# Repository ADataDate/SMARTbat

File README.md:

Meet Austin: the SMARTbat

Shoulder Mounted Anxiety Relieving Therapy Bat
==================================================================

Austin, the SMARTBat, is a shoulder mounted robot that monitors the wearer's **heart rate**, **oxygen saturation**, **respiration**, and **GSR** to build a live approximate model of the level of stress experienced by the wearer and autonomoulsy administers deep touch pressure therapy through a pnuematic vest when stress levels are out of normal range. Austin also monitors the social environment with verbal feedback on the "emotion" of the room using computer vision and tone analysis and names the faces it recognizes when queried. Communicating with Austin is possible thanks to the following Google Cloud services:

- [Speech-to-Text](https://cloud.google.com/speech-to-text)
- [Text-to-Speech](https://cloud.google.com/text-to-speech)

Austin is wrapped up in an adorably-cuddleable brown bat plushie that magnetically attaches to the wearer's shoulder and is programmed with physical(gestures) and emotional(RGB LED eyes) responses.

Repository Contents
-------------------

* **/Documents** - Images, reports, presentations, papers, etc
* **/Software** - Arduino sketches, Python scripts, and Log files
* **/Hardware** - Eagle files
* **/sensors_test** - UART Communication tests between devices

Documentation
-------------
To publish and subscribe to messages via MQTT, make sure you have an environment variable **CLOUDMQTT_URL:**
```bash
export CLOUDMQTT_URL=<url of your mqtt broker>
```
Python scripts also require the Eclipse Paho MQTT Python client library to be installed:
```bash
pip install --upgrade paho-mqtt
```

### Integration (+Austin)
First plug `Arduino` to your computer or raspberry pi on which you are going to run this python script.
Upload a sketch called `Software/stress_sensors_and_austin_emotes_ctrl/AustinOutput/AustinOutput.ino` to the `Arduino`.

To receive commands from MQTT and to forward the commands to Austin, just run

```
python Software/integration/subscriber.py --serial_port=<serial port of your arduino>
```

### Belt (Currently this is still under development due to hardware issue)
The belt has a separate sketch from that of Austin's.
Please upload a sketch called `Software/motion_control/motion_control.ino` to the other Arduino on the belt.

### Facial and Emotion Recognition
See [Facial and Emotion Recognition Documentation](https://github.com/Sayter99/face_recognition_ultra_light/blob/master/README.md).

### Voice User Interface (VUI)

The VUI requires a Google Cloud service account with access to the Cloud Speech-to-Text API and Cloud Text-to-Speech API. The location of the key file for the service account should be specified with the `GOOGLE_APPLICATION_CREDENTIALS` environment variable.

The VUI works with Python 3.7.1, and the required packages specific to the VUI can be installed as follows:
```bash
pip install --upgrade google-cloud-texttospeech
pip install --upgrade google-cloud-speech
pip install --upgrade pyaudio
pip install --upgrade pygame
```

To start the VUI, run the following:
```bash
cd ./Software/voice_user_interface
python main.py
```

### Stress Classifier

The stress classifier works with Python 3.7.1, and has no additional dependencies.

To start the stress classifier, run the following:
```bash
cd ./Software/stress_classifier
python stress_classifier.py
```

### Wearable Sensors

The arduino sketch **_Sensors_** serially outputs the heart rate, blood oxygen saturation, respiration and GSR data values which is read the script **_mqtt_on_body_sensors_pub_emotions_sub_**. This script then publishes the sensor data to a broker via MQTT.

Demonstration
-------------
* **Video to come**

License Information
-------------------

This product is _**open source**_!

Distributed as-is; no warranty is given. This is not a medical device and should not be used for the detection or prevention of disease, illness or otherwise.

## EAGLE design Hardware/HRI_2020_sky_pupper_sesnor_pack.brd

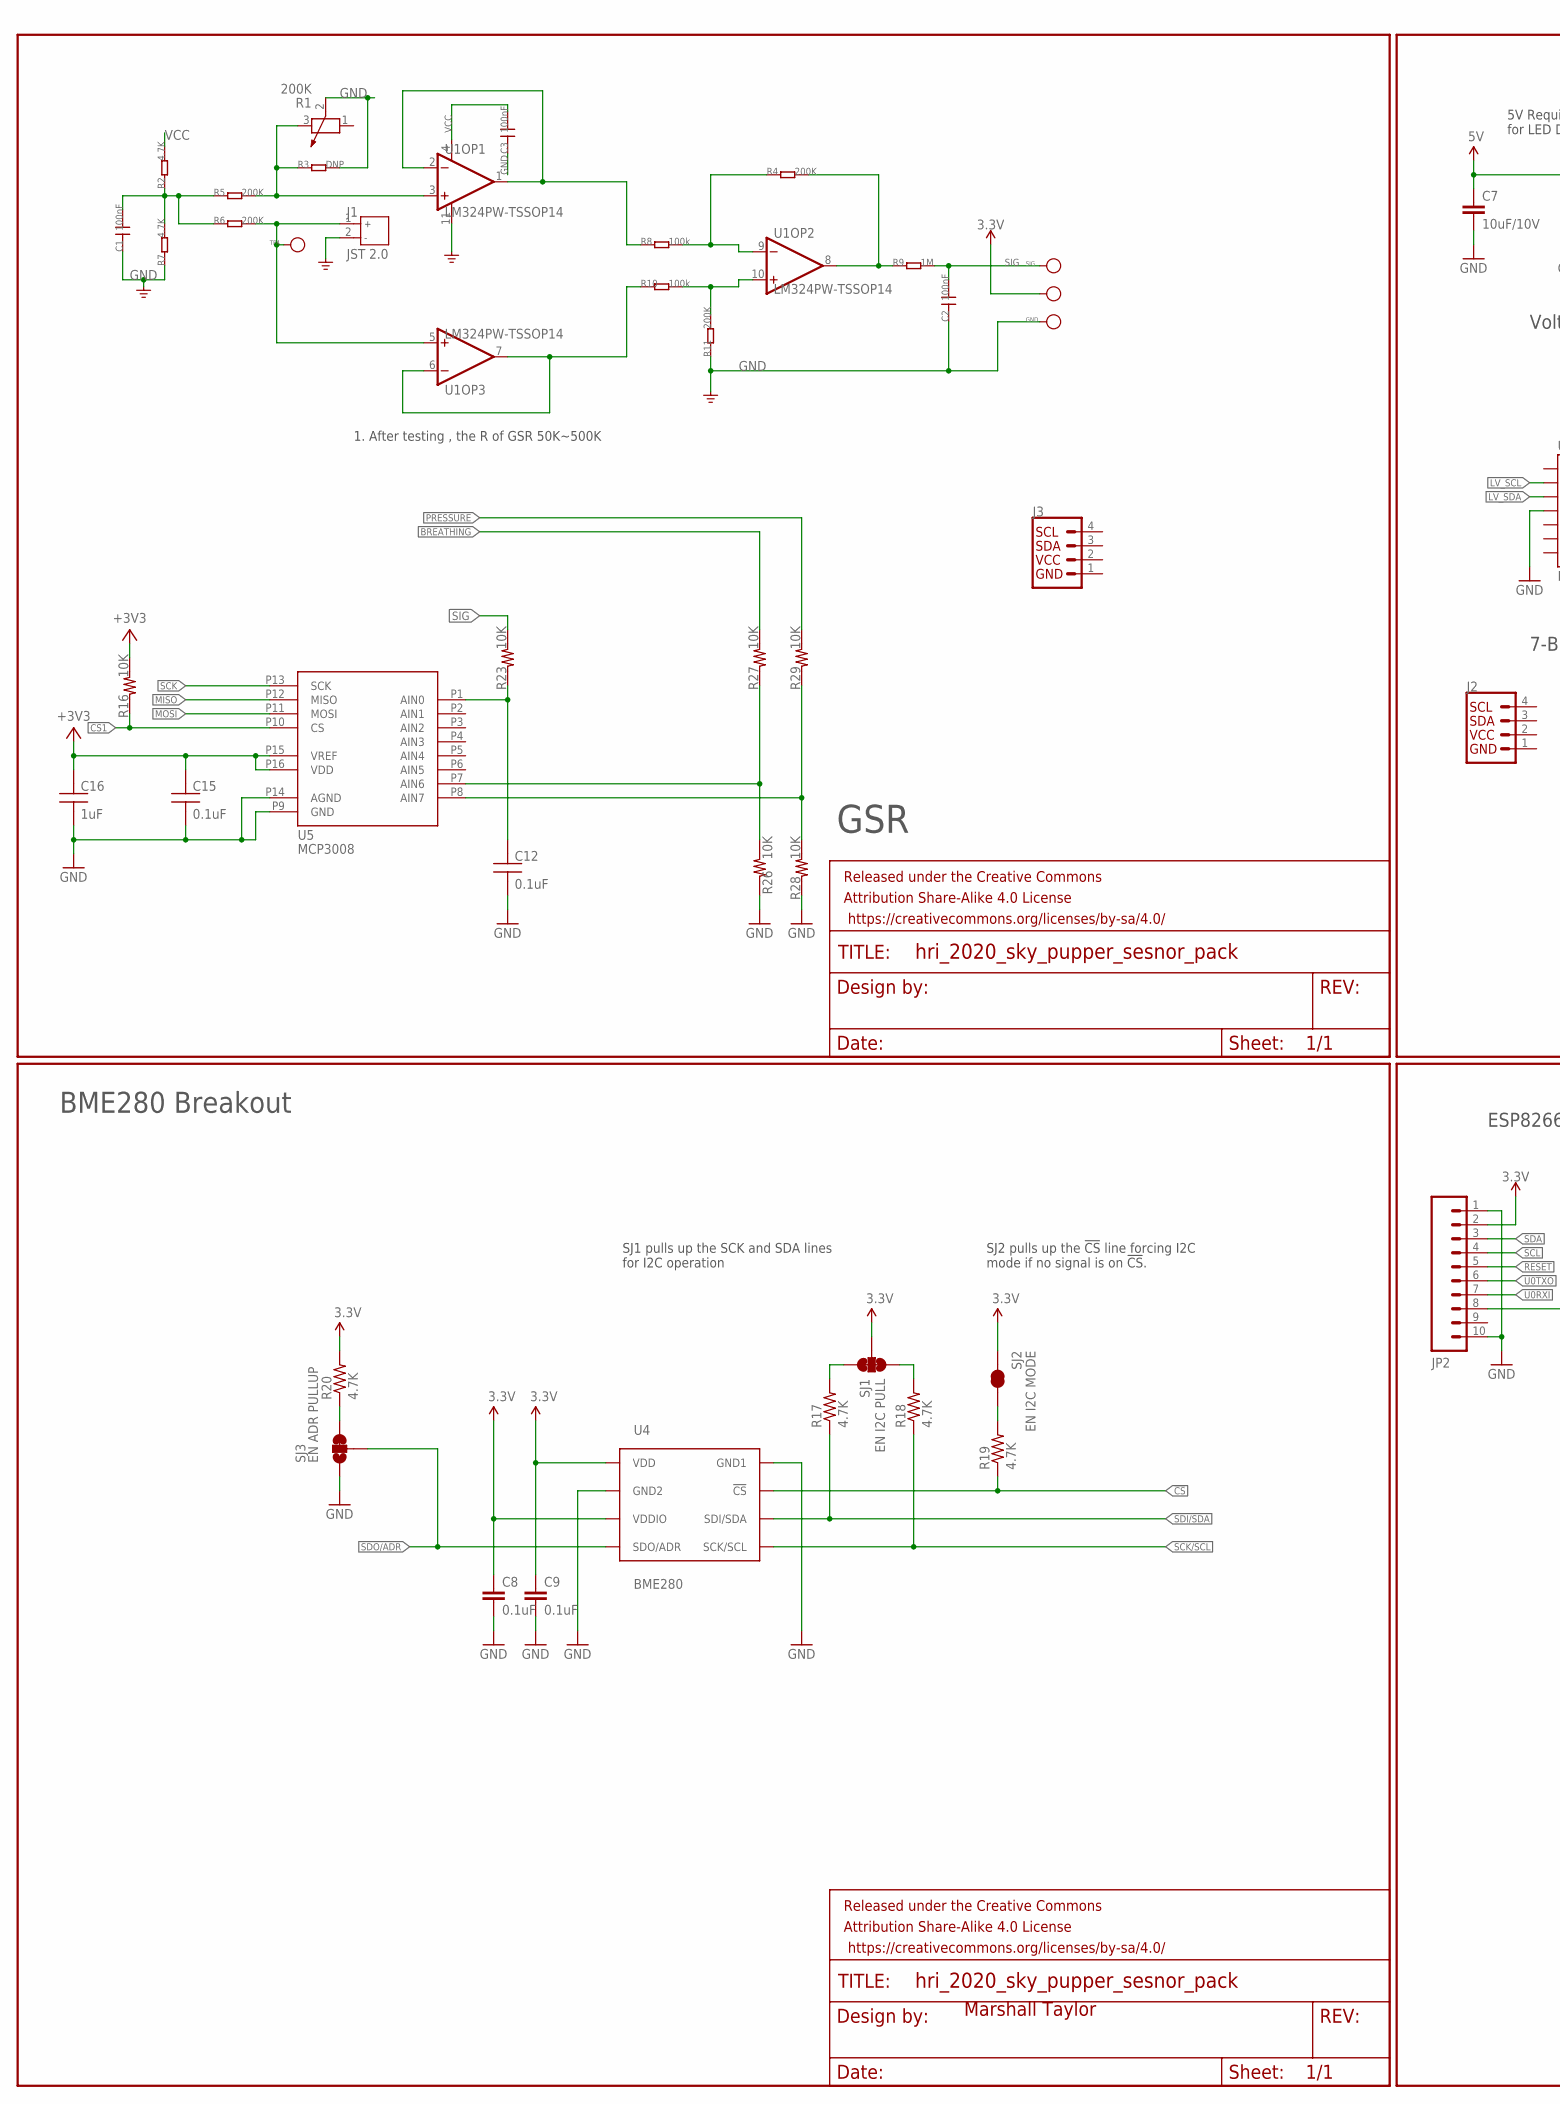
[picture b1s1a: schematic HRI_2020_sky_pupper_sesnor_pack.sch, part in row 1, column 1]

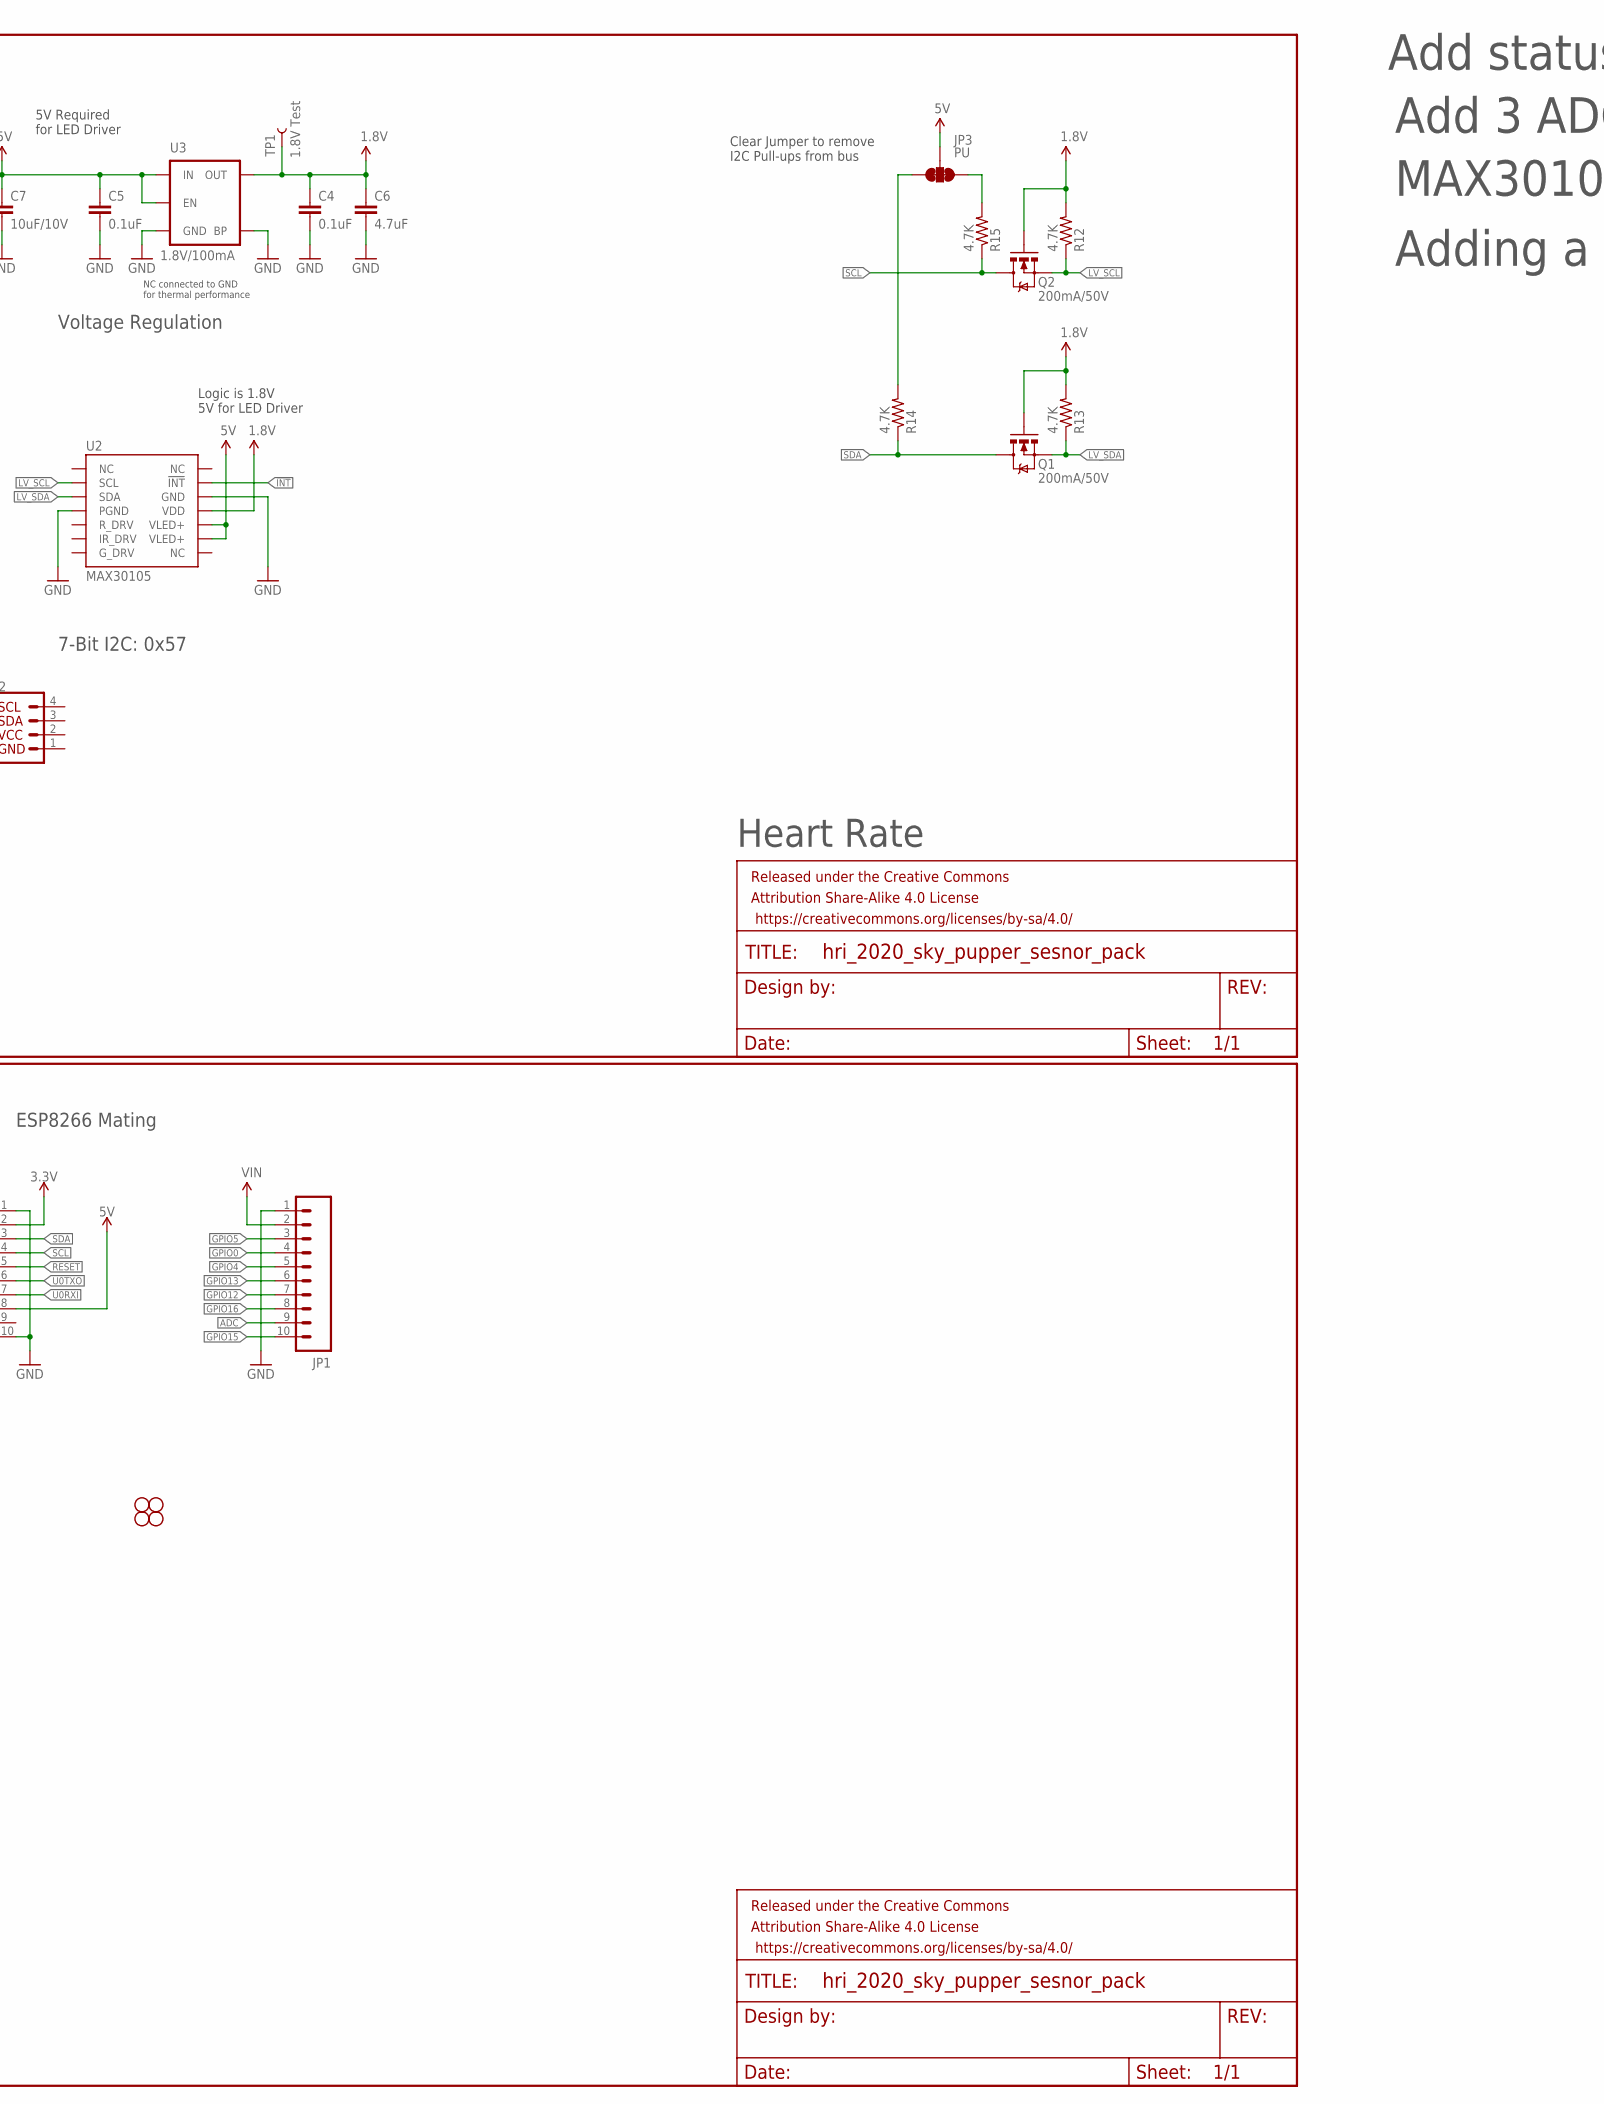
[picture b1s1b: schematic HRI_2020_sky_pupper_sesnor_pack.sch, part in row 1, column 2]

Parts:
C1, C2, C3: 100nF; 0603
C4, C5: 0.1uF; 0603-CAP@1
C6: 4.7uF; 0603-CAP@1
C7: 10uF/10V; 0805-CAP
C8, C9: 0.1uF; 0603-CAP
C12, C15: 0.1uF; 0603_SILK; PARTNO GRM188R70J104KA01D
C16: 1uF; 0603_SILK; PARTNO GRM188R70J104KA01D
FRAME1, FRAME2, FRAME3, FRAME4: FRAME-LETTERNO_PACKAGE; DUMMY
GND: PAD-TEST-POINT'4545'; TP_4545
J1: JST 2.0; JST-2.0
J2, J3: QWIIC_CONNECTORJS-1MM; 1X04_1MM_RA
JP1, JP2: M10NO_SILK_PTH_FEMALE; 1X10_NO_SILK
JP3: PU; PAD-JUMPER-3-3OF3_NC_BY_TRACE_YES_SILK_FULL_BOX
Q1, Q2: 200mA/50V; SOT23-3
R1: 200K; 3P-SMD-RECT-3.3X3.6
R2, R7: 4.7K; 0603
R3: DNP; 0603
R4, R5, R6, R11: 200K; 0603
R8, R10: 100k; 0603
R9: 1M; 0603
R12, R13, R14, R15, R17, R18, R19, R20: 4.7K; 0603-RES
R16, R23, R26, R27, R28, R29: 10K; 0603_SILK; PARTNO CR0603-FX-1002ELF
SIG: PAD-TEST-POINT'4545'; TP_4545
SJ1: EN I2C PULL; PAD-JUMPER-3-3OF3_NC_BY_TRACE_YES_SILK_FULL_BOX
SJ2: EN I2C MODE; PAD-JUMPER-2-NC_BY_TRACE_YES_SILK
SJ3: EN ADR PULLUP; PAD-JUMPER-3-2OF3_NC_BY_TRACE_YES_SILK_FULL_BOX
STANDOFF1, STANDOFF2, STANDOFF3, STANDOFF4: STAND-OFF
TP1: 1.8V Test; PAD.03X.04
TP4: PAD-TEST-POINT'4545'; TP_4545
U1: LM324PW-TSSOP14; TSSOP14
U2: MAX30105; OLGA-14
U3: 1.8V/100mA; SC70
U4: BME280; BME280_LGA
U5: MCP3008; SOIC-16
VCC: PAD-TEST-POINT'4545'; TP_4545

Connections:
1.8V: C4.1, C6.1, Q1.1 (G), Q2.1 (G), R12.2, R13.2, TP1.P$1, U2.11 (VDD), U3.5 (OUT)
3.3V: C8.1, C9.1, JP2.2, R20.2, SJ1.2, SJ2.2, U4.P$6 (VDDIO), U4.P$8 (VDD), VCC.T
5V: C5.1, C7.1, JP2.8, JP3.2, U2.9 (VLED+), U2.10 (VLED+), U3.1 (IN), U3.3 (EN)
!CS: R19.1, U4.P$2 (!CS)
!INT: U2.13 (!INT)
+3V3: C15.P1 (1), C16.P1 (1), R16.P2 (2), U5.P15 (VREF), U5.P16 (VDD)
ADC: JP1.9
BREATHING: R27.P2 (2)
CS1: R16.P1 (1), U5.P10 (CS)
GND: C1.1, C2.1, C3.1, C4.2, C5.2, C6.2, C7.2, C8.2, C9.2, C12.P2 (2), C15.P2 (2), C16.P2 (2), GND.T, J1.2, J2.1 (GND), J3.1 (GND), JP1.1, JP2.1, JP2.10, R1.2 (3), R3.2, R7.1, R11.1, R26.P1 (1), R28.P1 (1), SJ3.1, U1.11 (V-), U2.4 (PGND), U2.12 (GND), U3.2 (GND), U3.4 (BP), U4.P$1 (GND1), U4.P$7 (GND2), U5.P9 (GND), U5.P14 (AGND)
GPIO0: JP1.4
GPIO4: JP1.5
GPIO5: JP1.3
GPIO12: JP1.7
GPIO13: JP1.6
GPIO15: JP1.10
GPIO16: JP1.8
IN: J1.1, R6.2, TP4.T, U1.5 (IN+)
LV_SCL: Q2.2 (S), R12.1, U2.2 (SCL)
LV_SDA: Q1.2 (S), R13.1, U2.3 (SDA)
MISO: U5.P12 (MISO)
MOSI: U5.P11 (MOSI)
unnamed: R8.1, U1.1 (OUT), U1.2 (IN-)
unnamed: R10.1, U1.6 (IN-), U1.7 (OUT)
unnamed: R4.1, R8.2, U1.9 (IN-)
unnamed: R4.2, R9.1, U1.8 (OUT)
unnamed: R10.2, R11.2, U1.10 (IN+)
unnamed: C1.2, R2.1, R5.1, R6.1, R7.2
unnamed: R1.3 (2), R3.1, R5.2, U1.3 (IN+)
unnamed: JP3.1, R15.2
unnamed: JP3.3, R14.2
unnamed: R17.2, SJ1.3
unnamed: R18.2, SJ1.1
unnamed: R19.2, SJ2.1
unnamed: R20.1, SJ3.3
unnamed: R26.P2 (2), R27.P1 (1), U5.P7 (AIN6)
unnamed: R28.P2 (2), R29.P1 (1), U5.P8 (AIN7)
unnamed: C12.P1 (1), R23.P1 (1), U5.P1 (AIN0)
PRESSURE: R29.P2 (2)
RESET: JP2.5
SCK: U5.P13 (SCK)
SCK/SCL: R18.1, U4.P$4 (SCK/SCL)
SCL: JP2.4, Q2.3 (D), R15.1
SDA: JP2.3, Q1.3 (D), R14.1
SDI/SDA: R17.1, U4.P$3 (SDI/SDA)
SDO/ADR: SJ3.2, U4.P$5 (SDO/ADR)
SIG: C2.2, R9.2, R23.P2 (2), SIG.T
U0RXI: JP2.7
U0TXO: JP2.6
VCC: C3.2, J2.2 (VCC), J3.2 (VCC), R2.2, U1.4 (V+)
VIN: JP1.2

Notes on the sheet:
1. After testing , the R of GSR 50K~500K
7-Bit I2C: 0x57
Voltage Regulation
5V Required for LED Driver
Clear Jumper to remove I2C Pull-ups from bus
Logic is 1.8V 5V for LED Driver
NC connected to GND for thermal performance
GSR
Heart Rate
Marshall Taylor
BME280 Breakout
SJ1 pulls up the SCK and SDA lines for I2C operation
SJ2 pulls up the !CS! line forcing I2C mode if no signal is on !CS!.
ESP8266 Mating
Add status LEDs
Add 3 ADCs for repsiratory, GSR, Pressure
MAX30105 Needs mouse bite tear offs
Adding a connector wiring diagram for each sub circuit

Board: 2 copper layers, 66 parts (10 on the bottom side), 33 nets, no tracks yet.

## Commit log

2020-03-31 adding software folder for Arduino sketches and sensor data logs
2020-03-31 adding Documents folder for project posterity
2020-03-31 Adding Hardware folder to keep eagle files organized. Note: No new hardware will be ready because of long lead times on parts due to COVID-19. Committing for project posterity
2020-03-31 deleting files that were moved to folders
2020-04-02 adding integrated sensor sketch. TODO: Motor control
2020-04-02 Adding document for tracking systems integration
2020-04-02 Fixed crazy typos and nonsense wording
2020-04-02 removing keys
2020-04-02 Adding code for pressure sensor
2020-04-03 adding Respiration sensor sketch
2020-04-03 added a diagram ppt
2020-04-04 Adding code for deep breathing exercises
2020-04-07 adding senosr log file, updated integratedSensor sketch, and pressure sensing sketch
2020-04-07 Adding Alex's code for Austin's motor and LED functions
2020-04-07 Commiting daily baseline stress test data
2020-04-07 add face recognition submodule
2020-04-09 update face module
2020-04-09 update face recognition
2020-04-09 removing old sketches
2020-04-11 adding mqtt publisher, removing old Arduino Sketches, moving used Arduino sketches to new folder
2020-04-11 Adding publisher
2020-04-12 update face api
2020-04-12 adding broker URL to script
2020-04-12 working publisher
2020-04-12 added sleep
2020-04-12 moving client.subscribe to line 55
2020-04-12 working sub/pub
2020-04-14 Updating sketch to separate incoming/outgoing mesgs
2020-04-14 added scripts to subscribe to mqtt and publishes command to arduino
2020-04-14 Revert "[WIP] added scripts to subscribe to mqtt and publishes command to arduino"
2020-04-14 Revert "Merge pull request #2 from ADataDate/mqtt-to-arduino"
    This reverts commit 366d3cdb88102be1ca7646a8dd4df55ead986f95, reversing
    changes made to 45f4bc858cb24d0faea661ff7405870129155a27.
2020-04-15 Testing sammiches
2020-04-15 Managed to actuate Austin based on detected emotion
2020-04-23 adding sketch for calibration belt max pressure and motor control
2020-04-25 update face package
2020-04-26 updating motor control sketch, replacing serialevent with push button interrupt
2020-04-28 added rest of the subscribers
2020-04-28 update emotion publisher
2020-04-28 added more publishers for testing
2020-04-28 fixed typos
2020-04-28 update emotion recognition
2020-04-28 add emotion window for demo
2020-04-29 subscribe to all the topics
2020-04-29 fixed conflict
2020-04-29 add deleted file
2020-04-29 Add code for voice user interface
2020-04-29 Add code for stress classifier
2020-04-29 update face api to latest version
2020-04-29 added calibration callback
2020-04-29 added shake func if failed to process NLP
2020-04-29 Fix some bugs in the stress classifier prototype
2020-04-29 Make some minor changes
2020-04-30 Change response phrasing
2020-05-01 add document of face api
2020-05-01 Add details about the VUI and stress classifier to the README
2020-05-01 Make minor changes to README
2020-05-01 Make an even more minor change to the README
2020-05-02 add integration section
2020-05-02 working message mqtt code.
2020-05-02 updated subscriber to include arg_parse

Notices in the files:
parts and their libraries:
SparkFun-Capacitors: Licensing: Creative Commons ShareAlike 4.0 International - https://creativecommons.org/licenses/by-sa/4.0
SparkFun-Aesthetics: Released under the Creative Commons Attribution Share-Alike 4.0 License
SparkFun-Aesthetics: https://creativecommons.org/licenses/by-sa/4.0
